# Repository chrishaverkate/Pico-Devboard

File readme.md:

# Pico Devboard - v1.0.0
A very simple and generic development board for a Raspberry Pi Pico that leverages another Pico as a programmer and debugger. The development board is designed to make it simple and cheap to start programming on the Raspberry Pi Pico

**Fabrication Preview**

# Primary Features
* Pico soldered in as a [Pico Probe](https://github.com/raspberrypi/picoprobe)
* [ZIF](https://en.wikipedia.org/wiki/Zero_insertion_force) socket for holding the Pico being developed
* Room for small breadboard
* GPIO, Power, GND, and expansion header located by breadboard
* Probe points for power and ground
* Pico Dev board power switch

# Bill of Materials
*details coming*
* 2x [Raspberry Pi Pico](https://www.pishop.us/product/raspberry-pi-pico/) (U1 and in J4)
* [ZIF socket](https://www.adafruit.com/product/383) (J4)
* [Headers](https://a.co/d/4zF3gvf) (all 2.54mm pitch)
	* 1x - 1x26 GPIO (J2)
	* 2x - 1x3  power and programming (J1 and J5)
	* 1x - 2x10 off-board expansion (J3)
	* 1x - 1x4  test pins (J6)
* [Test Pins](https://a.co/d/6bz0lk5) (J6)
* [Slide switch](https://a.co/d/a2dGuMf) (SW2)
* [Push button](https://a.co/d/cavYAee) (SW1)
* LED (D1)
* Resistor (R1)
* [Breadboard](https://a.co/d/gGRnvQ6)
* [Rubber Standoffs](https://a.co/d/2oCXgiC)

# Ordering
I used [JLCPCB](https://jlcpcb.com) and could buy 10 boards for just under $16.

# Software
See the [Software Readme](software/pico-demo/readme.md)

# Resources
Need to collect links to helpful docs

# Errata
## 1) Serial RX/TX Flipped
**Description**: Serial RX/TX lines flipped from Pico Probe (U1) to Pico Dev (J4).
**Symptom if Uncorrected**: Serial communication will not work.
**Mitigation**:
1. Cut traces, on top of board, coming from U1 pins GP4 and GP5
2. Solder wires, on bottom of board:
	* U1 pin GP4 to J4 pin 2
	* U1 pin GP5 to J4 pin 1

## 2) J5 Silk Screen Misslabelled
**Description**: The labels for SWCLK and SWDIO on J5 are swapped.
**Symptom if Uncorrected**: Programming will fail with an error about the pico not responding.
**Mitigation**: Make correction when wiring

# Future Features
* Move or duplicate J2 to the right side of the breadboard
  * This will make it easier to connect GPIO directly to the off-board expansion header (J3)
* Add 2-pin jumper on 5V trace, between power switch (SW2) and power header (J1)
  * When the jumper is removed the power will be disconnected, allowing for in-line power measurement 

# Images

**Building**

**Built**

**Alive!**

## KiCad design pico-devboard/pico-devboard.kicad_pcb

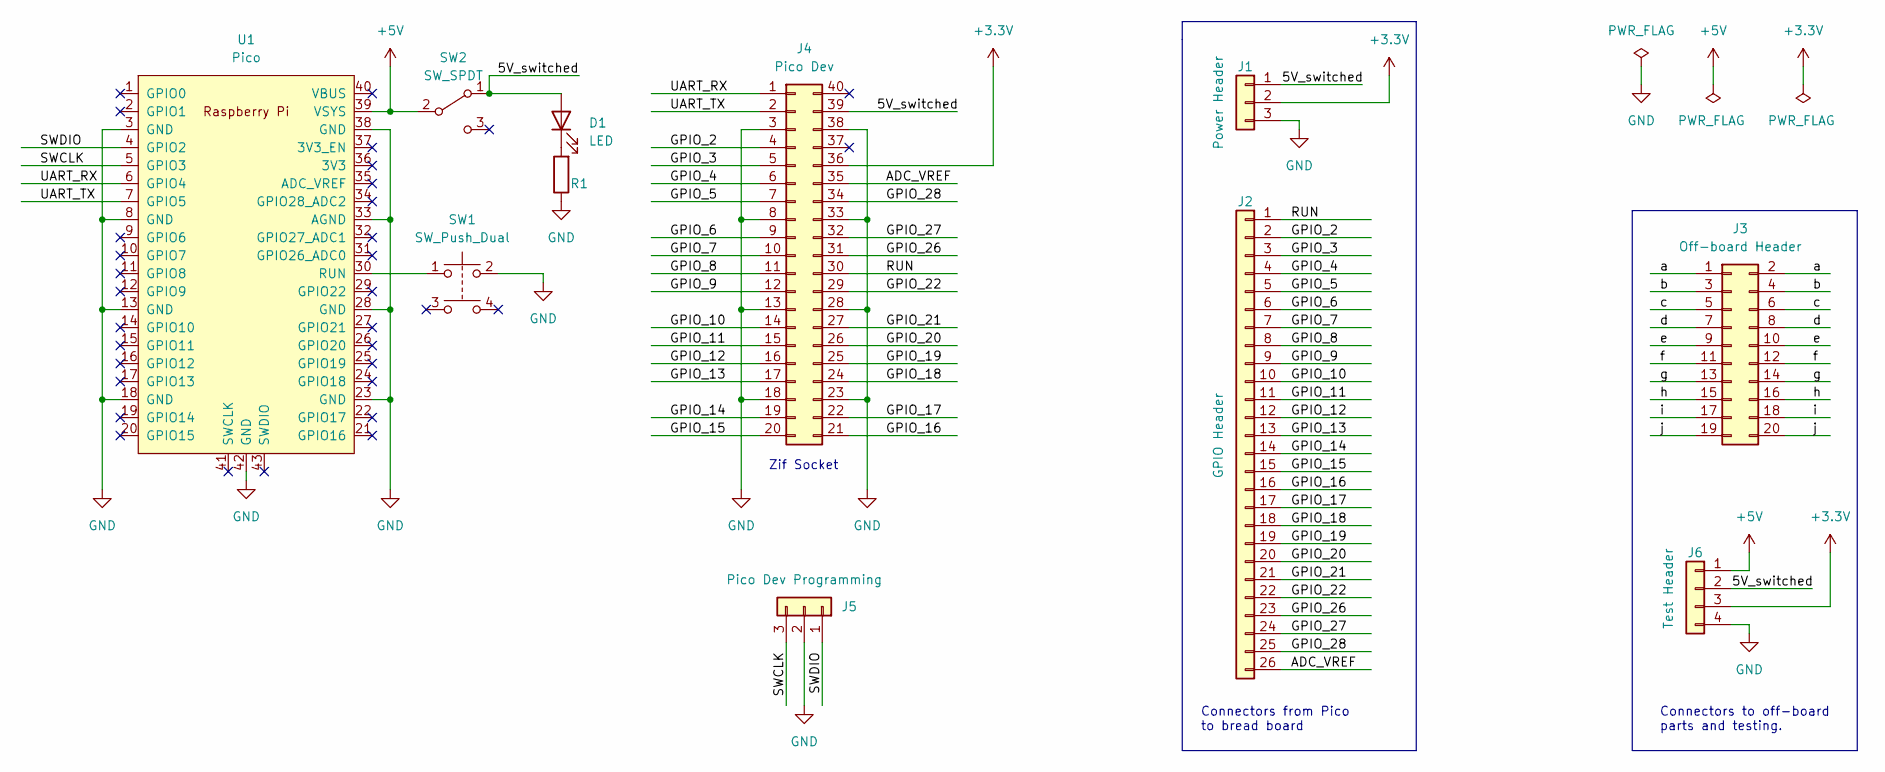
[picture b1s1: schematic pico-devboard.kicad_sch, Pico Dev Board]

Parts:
D1: LED; LED_D5.0mm
J1: Power Header; PinHeader_1x03_P2.54mm_Vertical
J2: GPIO Header; PinHeader_1x26_P2.54mm_Vertical
J3: Off-board Header; PinHeader_2x10_P2.54mm_Vertical
J4: Pico Dev; DIP_Socket-40_W11.9_W12.7_W15.24_W17.78_W18.5_3M_240-1280-0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
J5: Pico Dev Programming; PinHeader_1x03_P2.54mm_Vertical
J6: Test Header; PinHeader_1x04_P2.54mm_Vertical
R1: R; R_Axial_DIN0411_L9.9mm_D3.6mm_P15.24mm_Horizontal
SW1: SW_Push_Dual; SW_PUSH_6mm_H8mm
SW2: SW_SPDT; sw_slide_vert_SPDT
U1: Pico; RPi_Pico_SMD_TH

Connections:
+3V3: J1.2, J4.36, J6.3
+5V: J6.1, SW2.2 (B), U1.39 (VSYS)
/5V_switched: D1.2 (A), J1.1, J4.39, J6.2, SW2.1 (A)
/ADC_VREF: J2.26, J4.35
/GPIO_2: J2.2, J4.4
/GPIO_3: J2.3, J4.5
/GPIO_4: J2.4, J4.6
/GPIO_5: J2.5, J4.7
/GPIO_6: J2.6, J4.9
/GPIO_7: J2.7, J4.10
/GPIO_8: J2.8, J4.11
/GPIO_9: J2.9, J4.12
/GPIO_10: J2.10, J4.14
/GPIO_11: J2.11, J4.15
/GPIO_12: J2.12, J4.16
/GPIO_13: J2.13, J4.17
/GPIO_14: J2.14, J4.19
/GPIO_15: J2.15, J4.20
/GPIO_16: J2.16, J4.21
/GPIO_17: J2.17, J4.22
/GPIO_18: J2.18, J4.24
/GPIO_19: J2.19, J4.25
/GPIO_20: J2.20, J4.26
/GPIO_21: J2.21, J4.27
/GPIO_22: J2.22, J4.29
/GPIO_26: J2.23, J4.31
/GPIO_27: J2.24, J4.32
/GPIO_28: J2.25, J4.34
/RUN: J2.1, J4.30
/SWCLK: J5.3, U1.5 (GPIO3)
/SWDIO: J5.1, U1.4 (GPIO2)
/UART_RX: J4.1, U1.6 (GPIO4)
/UART_TX: J4.2, U1.7 (GPIO5)
/a: J3.1, J3.2
/b: J3.3, J3.4
/c: J3.5, J3.6
/d: J3.7, J3.8
/e: J3.9, J3.10
/f: J3.11, J3.12
/g: J3.13, J3.14
/h: J3.15, J3.16
/i: J3.17, J3.18
/j: J3.19, J3.20
GND: J1.3, J4.3, J4.8, J4.13, J4.18, J4.23, J4.28, J4.33, J4.38, J5.2, J6.4, R1.1, SW1.2, U1.3 (GND), U1.8 (GND), U1.13 (GND), U1.18 (GND), U1.23 (GND), U1.28 (GND), U1.33 (AGND), U1.38 (GND), U1.42 (GND)
unnamed: D1.1 (K), R1.2
unnamed: SW1.1, U1.30 (RUN)

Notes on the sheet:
Connectors from Pico to bread board
Connectors to off-board parts and testing.
Zif Socket

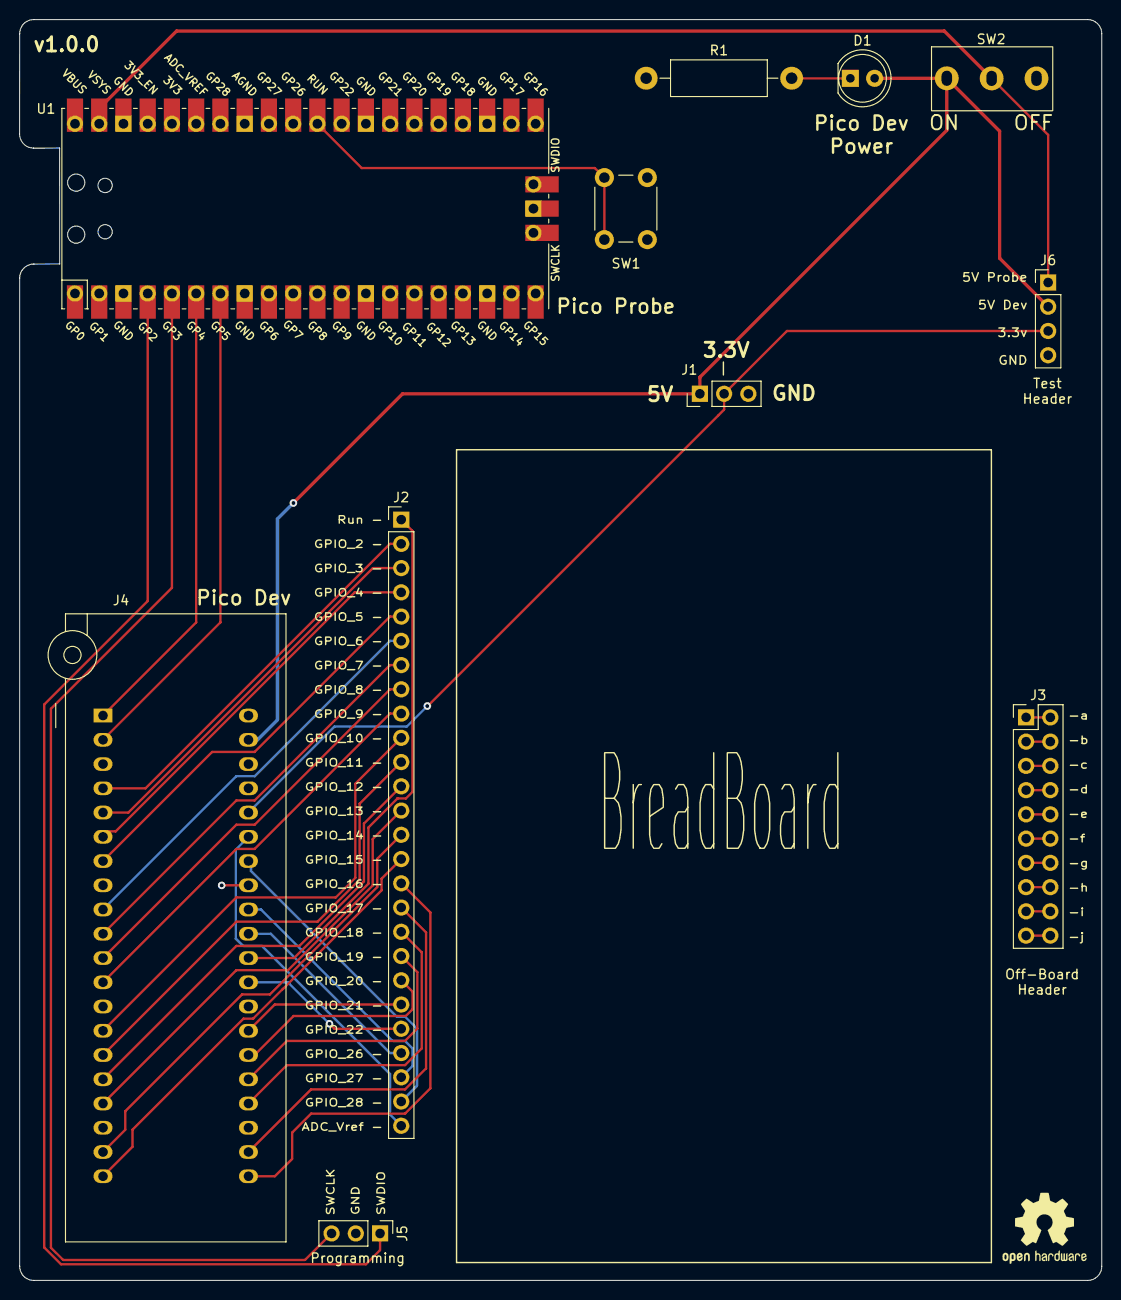
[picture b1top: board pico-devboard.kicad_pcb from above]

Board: 2 copper layers, 113.4 x 132.1 mm, 11 parts (0 on the bottom side), 46 nets.

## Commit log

2023-03-04 Finally starting git
2023-03-05 Silkscreen, small adjustments, readme updates
2023-03-08 Fixing header spacing issue and re-routing
2023-03-11 v1.0.0 fab files
2023-03-11 Updating readme
2023-03-11 Adding test pins link to readme
2023-03-11 Fixing link
2023-04-01 Initial software.
    Adding a demo software project.
2023-04-01 Adding some more docs and images
2023-04-30 Adding a couple ideas for next rev of board
